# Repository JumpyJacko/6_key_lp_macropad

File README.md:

# A 6 Key (+ Rotary Encoder) Low-Profile Macropad
Designed by a person who doesn't know how to design a PCB (thanks aio3 for the guide and all the other resources I used).

Made because I had 6 keyswitches leftover and wanted to try my hand at designing a PCB.

The firmware for this macropad can be found on my fork of [qmk](https://github.com/qmk/qmk_firmware), which can be found [here](https://github.com/JumpyJacko/qmk_firmware/tree/master/keyboards/6klpm).

# Gallery
### The PCB

### The Schematic

# Extras
Please tell me if I did something wrong, I'm honestly not too sure if any of this PCB is correct.

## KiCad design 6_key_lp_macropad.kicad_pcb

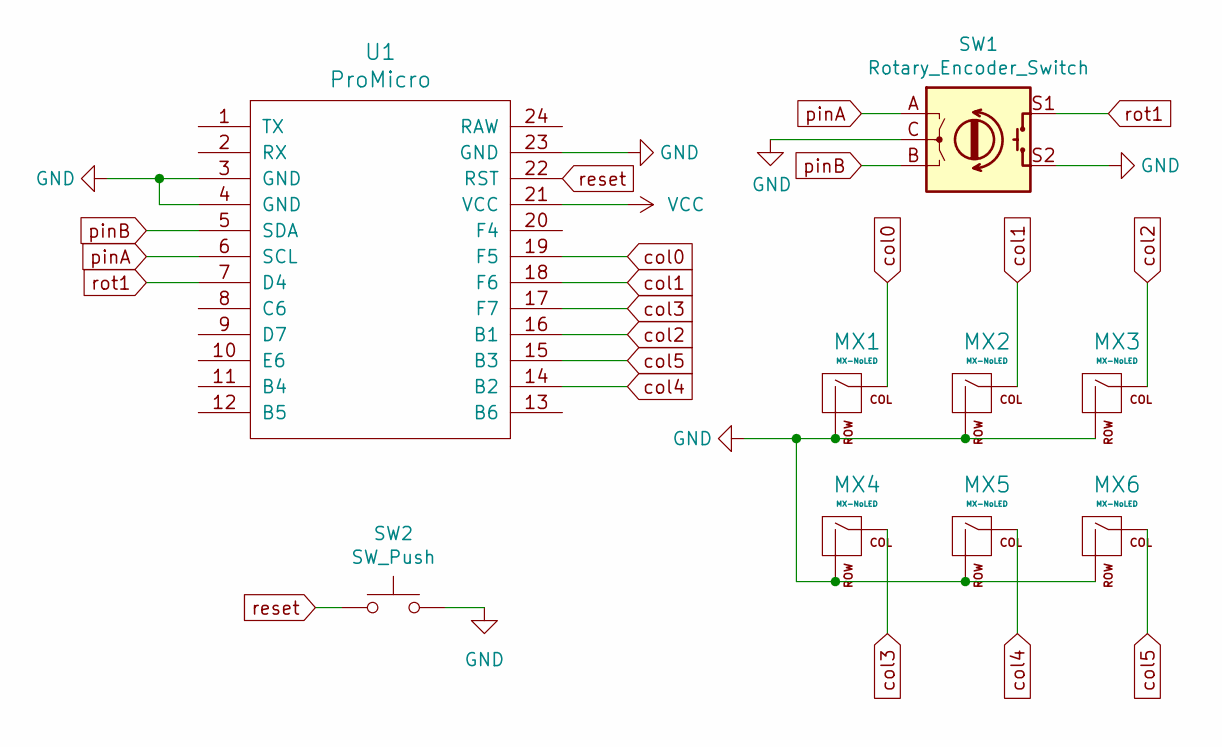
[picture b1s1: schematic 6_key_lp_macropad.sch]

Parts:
MX1, MX2, MX3, MX4, MX5, MX6: MX-NoLED; KailhChoc-1U
SW1: Rotary_Encoder_Switch; RotaryEncoder_Alps_EC11E-Switch_Vertical_H20mm
SW2: SW_Push; SKQG-1155865
U1: ProMicro; ProMicro-NoSilk

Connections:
GND: MX1.2 (ROW), MX2.2 (ROW), MX3.2 (ROW), MX4.2 (ROW), MX5.2 (ROW), MX6.2 (ROW), SW1.C, SW1.S2, SW2.2, U1.3 (GND), U1.4 (GND), U1.23 (GND)
VCC: U1.21 (VCC)
col0: MX1.1 (COL), U1.19 (F5)
col1: MX2.1 (COL), U1.18 (F6)
col2: MX3.1 (COL), U1.16 (B1)
col3: MX4.1 (COL), U1.17 (F7)
col4: MX5.1 (COL), U1.14 (B2)
col5: MX6.1 (COL), U1.15 (B3)
pinA: SW1.A, U1.6 (SCL)
pinB: SW1.B, U1.5 (SDA)
reset: SW2.1, U1.22 (RST)
rot1: SW1.S1, U1.7 (D4)

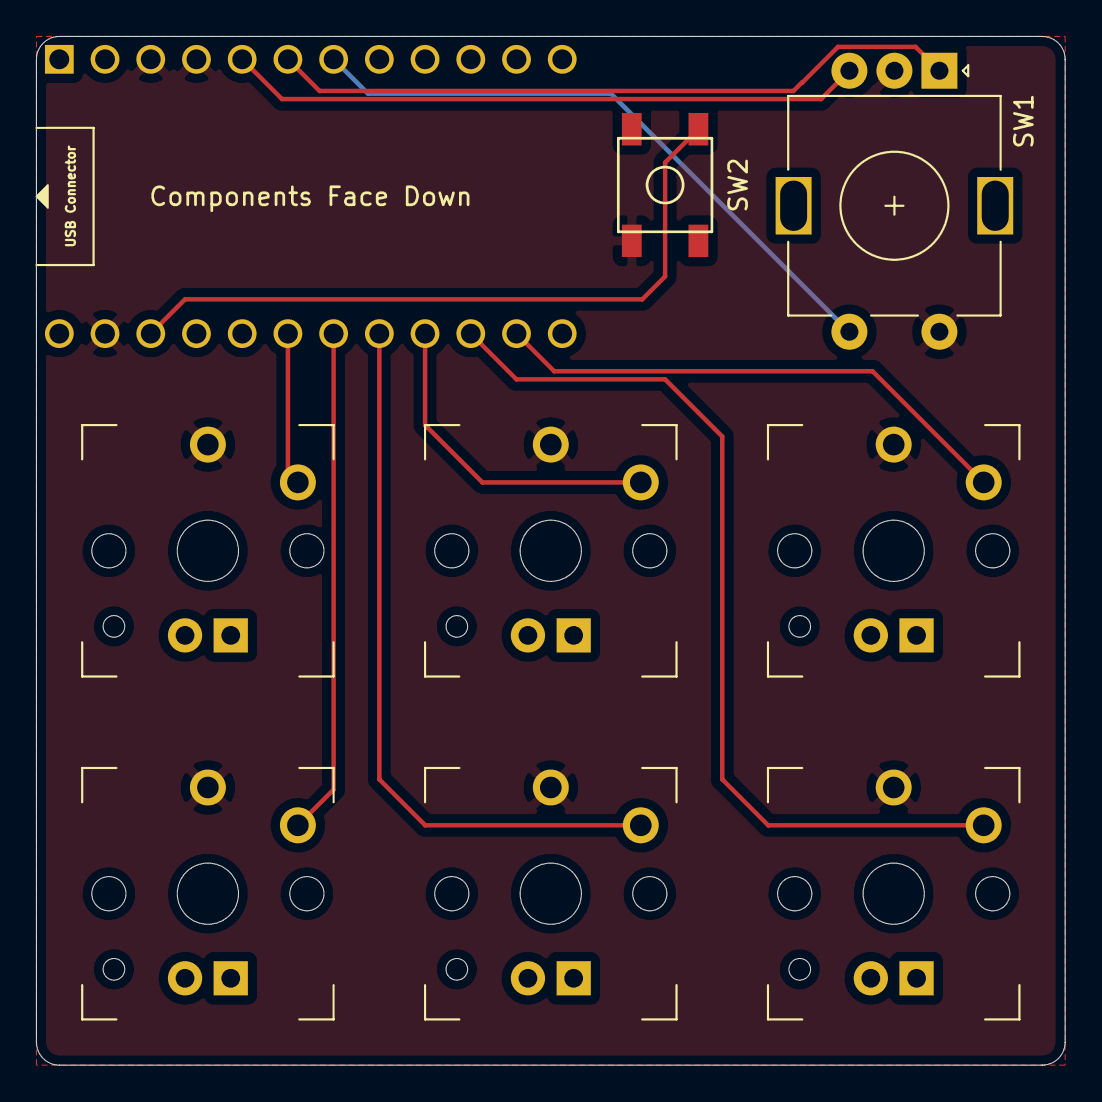
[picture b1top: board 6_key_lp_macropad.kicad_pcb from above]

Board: 2 copper layers, 57.2 x 57.2 mm, 9 parts (1 on the bottom side), 11 nets.

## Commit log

2022-07-09 Inital commit
2022-07-09 Add submodules
2022-07-09 Added libraries
2022-07-12 Matrix Schema
2022-07-12 Changed to Direct Pin assignment
2022-07-12 Made the first PCB version
2022-07-12 Added README.md
2022-07-12 Flipped MCU to allow for stronger USB connector
2022-07-13 Fixed Ground Fills and Added Gerbers
2022-07-13 Corrected for direct pin assignment
2022-07-13 Added firmware link
